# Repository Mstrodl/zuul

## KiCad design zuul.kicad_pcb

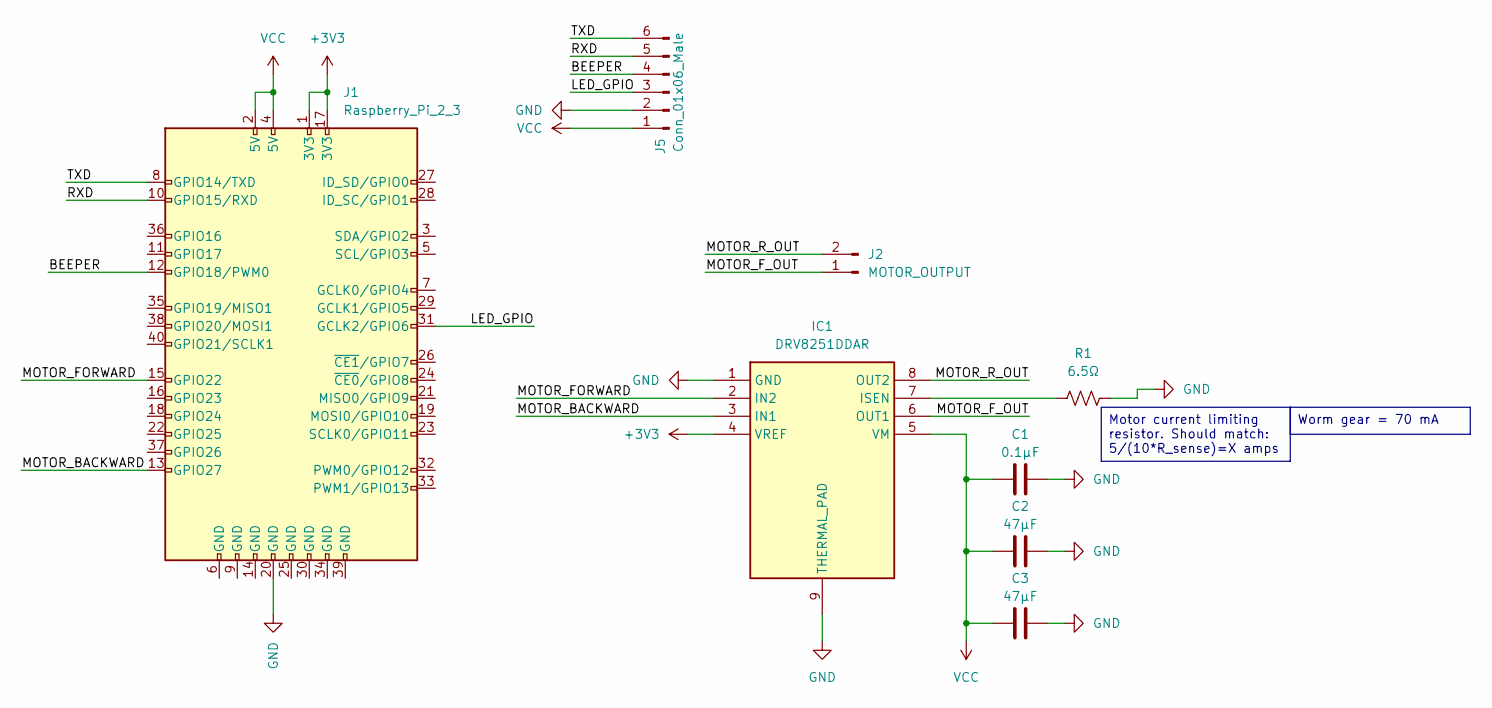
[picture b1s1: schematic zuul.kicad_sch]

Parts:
C1: 0.1μF; C_0402_1005Metric
C2, C3: 47μF; C_0805_2012Metric
IC1: DRV8251DDAR; SOIC127P600X170-9N; Manufacturer_Part_Number DRV8251DDAR; Mouser Part Number 595-DRV8251DDAR
J1: Raspberry_Pi_2_3; PinSocket_2x20_P2.54mm_Vertical
J2: MOTOR_OUTPUT; CUSTOM_PIN_HEADER_01x02_J2
J5: Conn_01x06_Male; JST_XH_S6B-XH-A_1x06_P2.50mm_Horizontal
R1: 6.5Ω; R_1206_3216Metric

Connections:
+3V3: IC1.4 (VREF), J1.1 (3V3), J1.17 (3V3)
/BEEPER: J1.12 (GPIO18/PWM0), J5.4
/LED_GPIO: J1.31 (GCLK2/GPIO6), J5.3
/MOTOR_BACKWARD: IC1.3 (IN1), J1.13 (GPIO27)
/MOTOR_FORWARD: IC1.2 (IN2), J1.15 (GPIO22)
/MOTOR_F_OUT: IC1.6 (OUT1), J2.1
/MOTOR_R_OUT: IC1.8 (OUT2), J2.2
/RXD: J1.10 (GPIO15/RXD), J5.5
/TXD: J1.8 (GPIO14/TXD), J5.6
GND: C1.2, C2.2, C3.2, IC1.1 (GND), IC1.9 (THERMAL_PAD), J1.20 (GND), J5.2, R1.2
unnamed: IC1.7 (ISEN), R1.1
VCC: C1.1, C2.1, C3.1, IC1.5 (VM), J1.2 (5V), J1.4 (5V), J5.1

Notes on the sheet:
Motor current limiting resistor. Should match: 5/(10*R_sense)=X amps
Worm gear = 70 mA

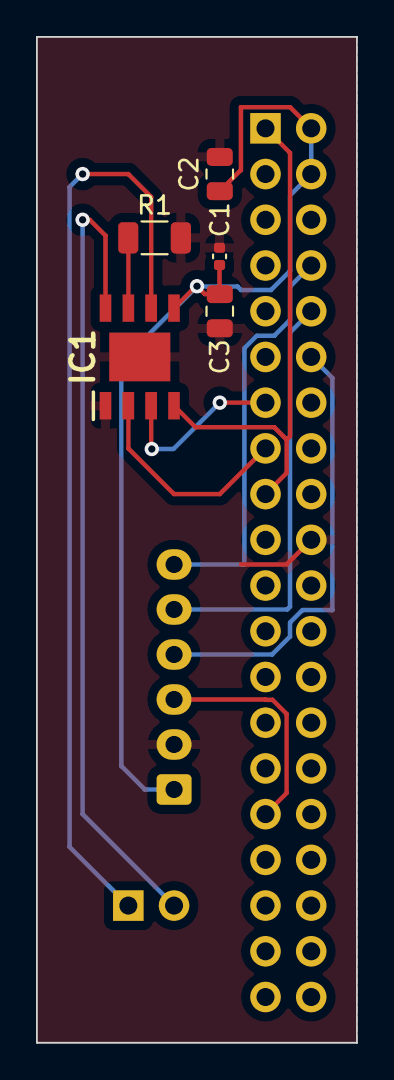
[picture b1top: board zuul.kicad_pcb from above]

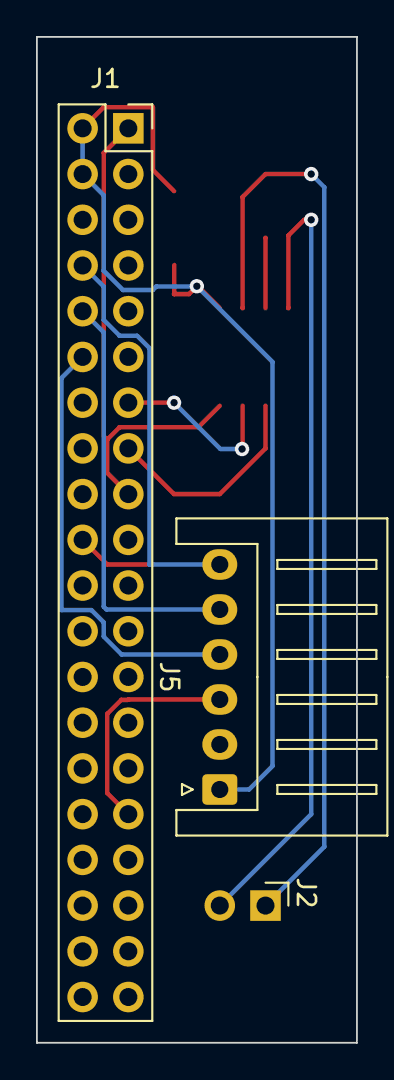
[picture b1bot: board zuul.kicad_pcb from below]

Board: 2 copper layers, 17.8 x 55.9 mm, 8 parts (3 on the bottom side), 12 nets.

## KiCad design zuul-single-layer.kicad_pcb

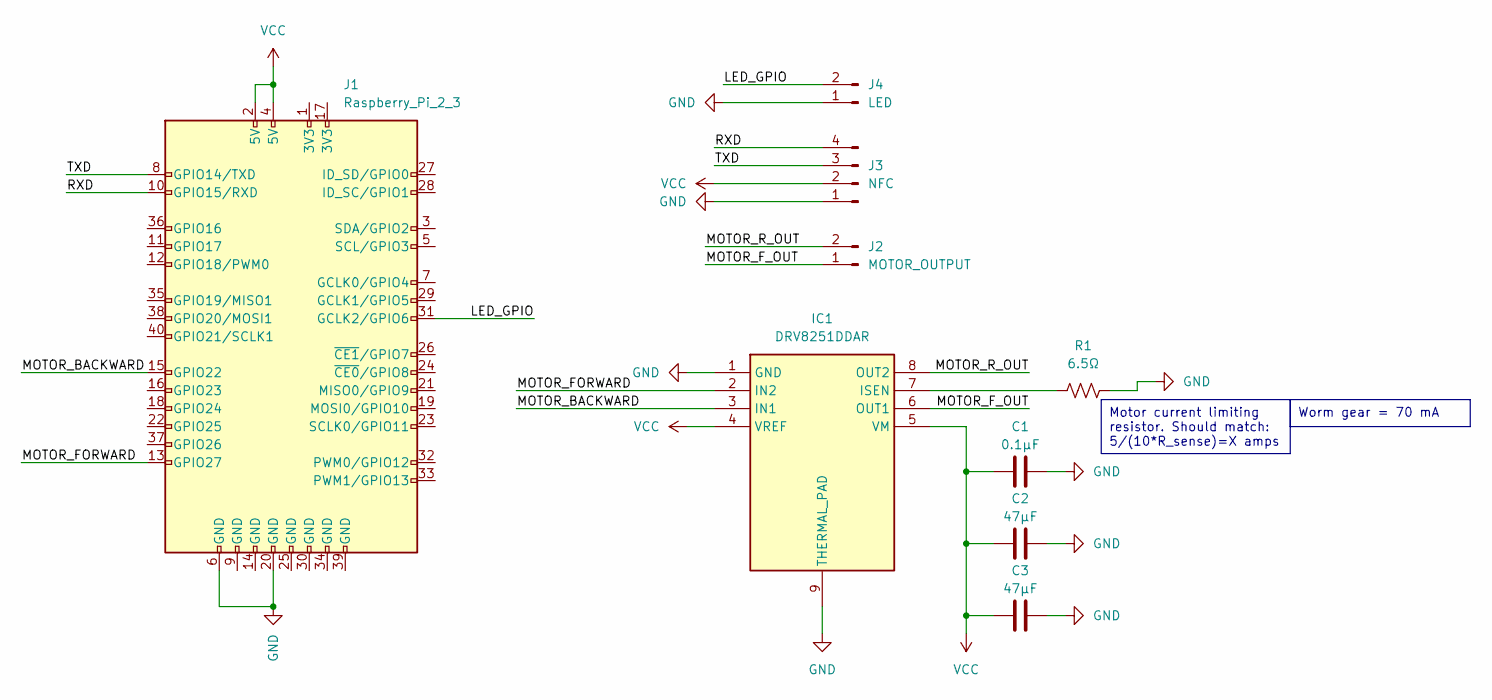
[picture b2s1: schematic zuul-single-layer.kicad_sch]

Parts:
C1: 0.1μF; C_0402_1005Metric
C2, C3: 47μF; C_0805_2012Metric
IC1: DRV8251DDAR; SOIC127P600X170-9N; Manufacturer_Part_Number DRV8251DDAR; Mouser Part Number 595-DRV8251DDAR
J1: Raspberry_Pi_2_3; PinSocket_2x20_P2.54mm_Vertical
J2: MOTOR_OUTPUT; CUSTOM_PIN_HEADER_01x02_J2
J3: NFC; CUSTOM_PinHeader_1x04_P2.54mm_Horizontal
J4: LED; CUSTOM_PIN_HEADER_01x02_J2
R1: 6.5Ω; R_1206_3216Metric

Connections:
/LED_GPIO: J1.31 (GCLK2/GPIO6), J4.2
/MOTOR_BACKWARD: IC1.3 (IN1), J1.15 (GPIO22)
/MOTOR_FORWARD: IC1.2 (IN2), J1.13 (GPIO27)
/MOTOR_F_OUT: IC1.6 (OUT1), J2.1
/MOTOR_R_OUT: IC1.8 (OUT2), J2.2
/RXD: J1.10 (GPIO15/RXD), J3.4
/TXD: J1.8 (GPIO14/TXD), J3.3
GND: C1.2, C2.2, C3.2, IC1.1 (GND), IC1.9 (THERMAL_PAD), J1.6 (GND), J1.20 (GND), J3.1, J4.1, R1.2
unnamed: IC1.7 (ISEN), R1.1
VCC: C1.1, C2.1, C3.1, IC1.4 (VREF), IC1.5 (VM), J1.2 (5V), J1.4 (5V), J3.2

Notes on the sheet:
Motor current limiting resistor. Should match: 5/(10*R_sense)=X amps
Worm gear = 70 mA

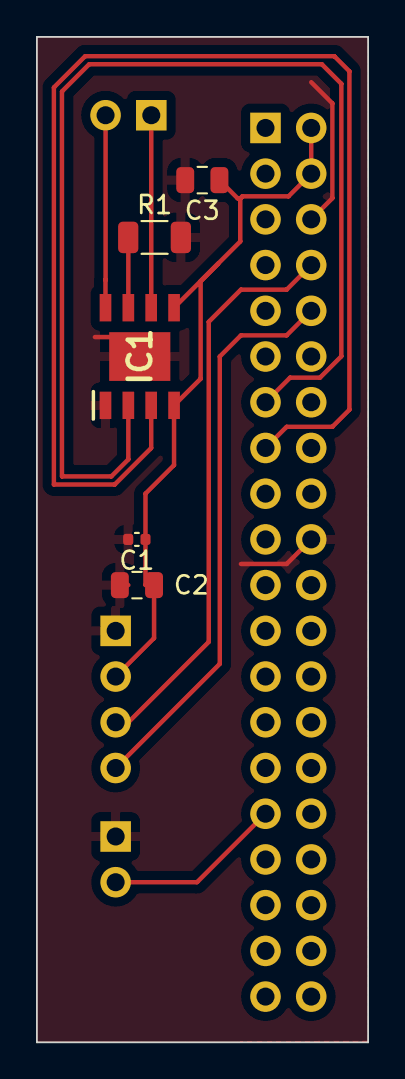
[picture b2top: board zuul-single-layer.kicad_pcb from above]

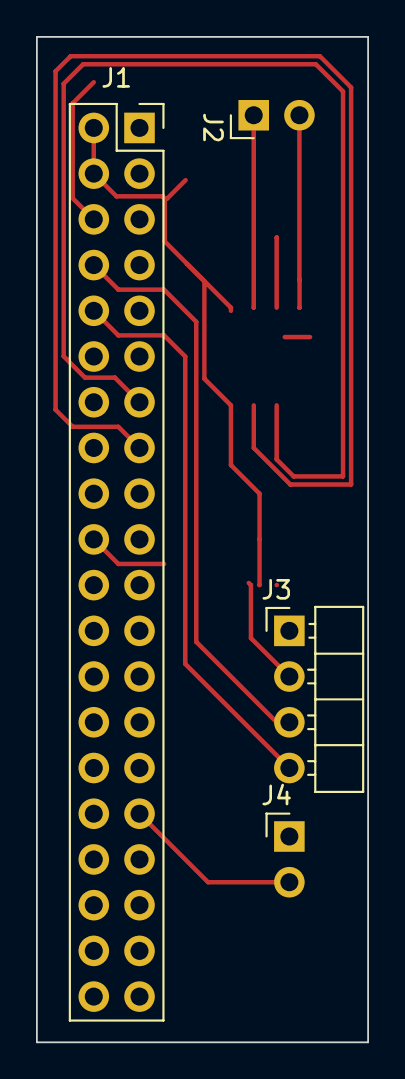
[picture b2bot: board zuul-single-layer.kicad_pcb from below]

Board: 2 copper layers, 18.4 x 55.9 mm, 9 parts (4 on the bottom side), 10 nets.

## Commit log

2023-08-27 chom
2024-02-18 compuger
2025-04-13 ummm
